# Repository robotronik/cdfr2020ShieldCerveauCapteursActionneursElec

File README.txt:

Ce fichier a pour but d'expliciter les différents composants de la carte électronique afin d'en faciliter la compréhension.

LevelShifter_ToF :

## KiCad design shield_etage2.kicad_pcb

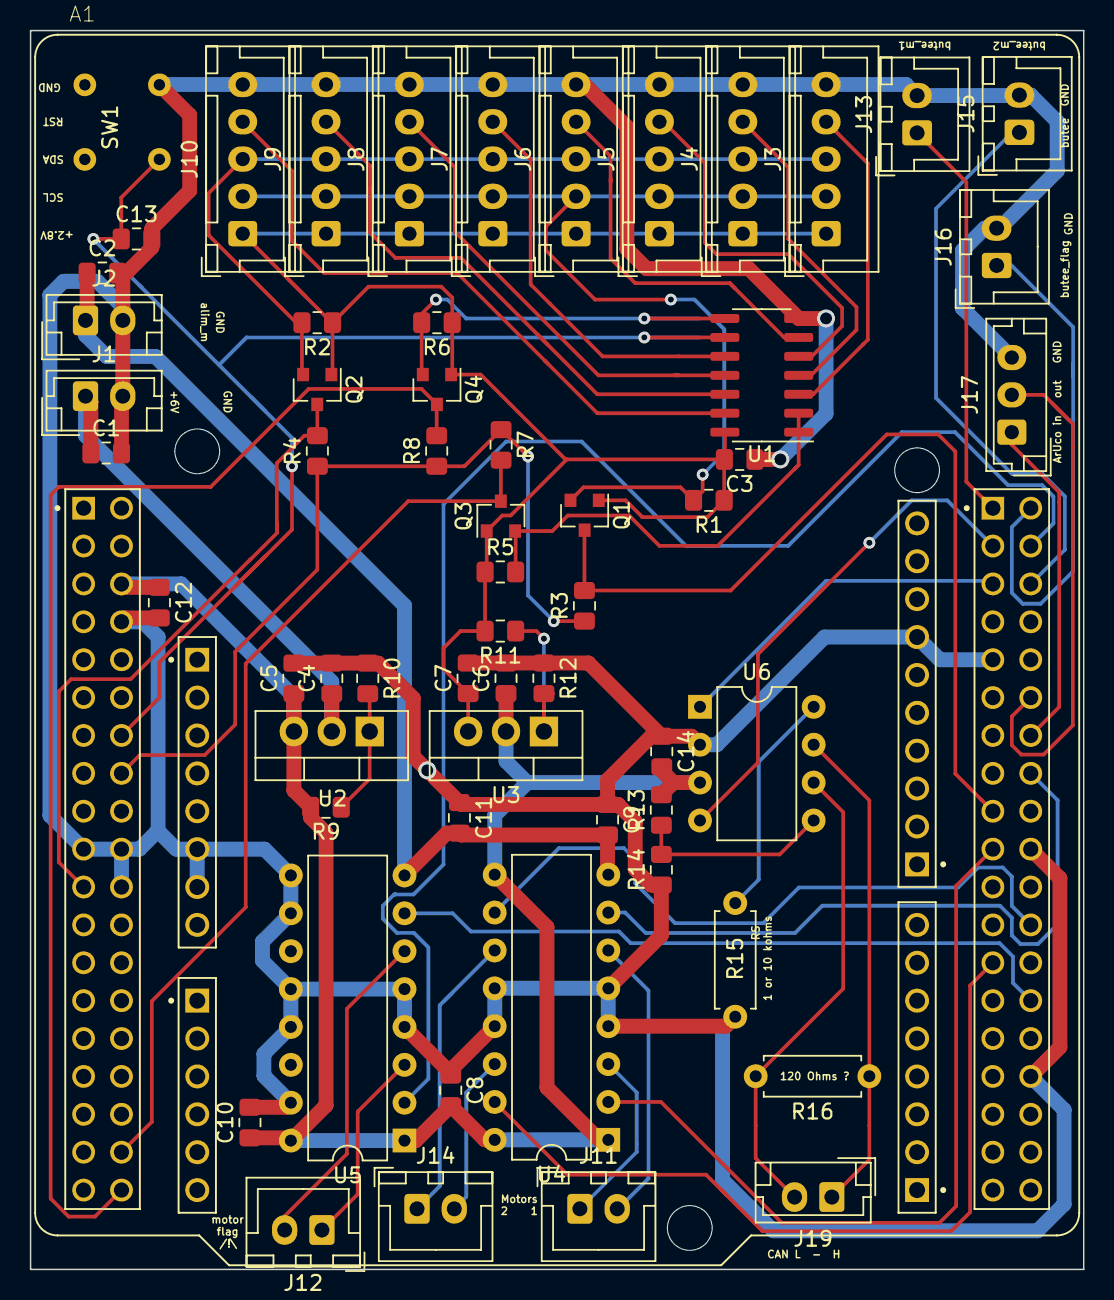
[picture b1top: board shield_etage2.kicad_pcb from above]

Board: 2 copper layers, 70.6 x 83.1 mm, 60 parts (0 on the bottom side), 48 nets.

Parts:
A1: NUCLEO-F401RE; ST_NUCLEO-F401RE
C1, C2, C3, C4, C6, C8, C9, C10, C11, C13, C14: 100n; C_0805_2012Metric_Pad1.15x1.40mm_HandSolder
C5, C7, C12: 1µ; C_0805_2012Metric_Pad1.15x1.40mm_HandSolder
J1, J2: Conn_01x02; JST_EH_B2B-EH-A_1x02_P2.50mm_Vertical
J3, J4, J5, J6, J7, J8, J9, J10: ToF; JST_XH_B5B-XH-A_1x05_P2.50mm_Vertical
J11, J12, J14: Moteur; JST_XH_B2B-XH-A_1x02_P2.50mm_Vertical
J13, J15, J16: butee; JST_XH_B2B-XH-A_1x02_P2.50mm_Vertical
J17: Conn_01x03-Connector_Generic-shield_etage2-rescue; JST_EH_B3B-EH-A_1x03_P2.50mm_Vertical
J19: output_CAN; JST_EH_B2B-EH-A_1x02_P2.50mm_Vertical
Q1, Q2, Q3, Q4: BSS138; SOT-23
R1, R2, R3, R4, R5, R6, R7, R8: Pull; R_0805_2012Metric_Pad1.15x1.40mm_HandSolder
R9: 1k; R_0805_2012Metric_Pad1.15x1.40mm_HandSolder
R10: 3k; R_0805_2012Metric_Pad1.15x1.40mm_HandSolder
R11: 240; R_0805_2012Metric_Pad1.15x1.40mm_HandSolder
R12: 300; R_0805_2012Metric_Pad1.15x1.40mm_HandSolder
R13, R14: 470; R_0805_2012Metric_Pad1.15x1.40mm_HandSolder
R15: 10k; R_Axial_DIN0207_L6.3mm_D2.5mm_P7.62mm_Horizontal
R16: 120; R_Axial_DIN0207_L6.3mm_D2.5mm_P7.62mm_Horizontal
SW1: SW_Push; 5x5
U1: 74HC164; SOIC-14_3.9x8.7mm_P1.27mm
U2, U3: LM317_TO3; TO-220-3_Vertical
U4, U5: L293D; DIP-16_W7.62mm
U6: MCP2551-I-P; DIP-8_W7.62mm

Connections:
+2V8: C3.2, C7.1, J3.1, J4.1, J5.1, J6.1, J7.1, J8.1, J9.1, J10.1, Q1.1, Q2.1, Q3.1, Q4.1, R1.1, R2.1, R5.1, R6.1, R11.2, U1.14, U3.3
+3V3: A1.CN7_16, R3.1, R4.1, R7.1, R8.1
+5V: A1.CN7_6, C5.1, C6.1, C8.2, C10.1, C12.1, C14.2, R9.2, R13.2, U2.3, U3.2, U4.1, U4.9, U4.16, U5.1, U5.16, U6.3
+6V: C1.1, C4.1, J1.1, U2.2
/ArUco.sch/ArUco1: A1.CN10_14, J17.1
/ArUco.sch/ArUco2: A1.CN10_12, J17.2
/Driver_moteurs/moteur1_pin1: J11.1, U4.3
/Driver_moteurs/moteur1_pin2: J11.2, U4.6
/Driver_moteurs/moteur2_pin1: J14.1, U4.11
/Driver_moteurs/moteur2_pin2: J14.2, U4.14
/Driver_moteurs/moteur3_pin1: J12.1, U5.3
/Driver_moteurs/moteur3_pin2: J12.2, U5.6
/Driver_moteurs/pwm_bras1: A1.CN10_19, U4.2
/Driver_moteurs/pwm_bras2: A1.CN10_24, U4.10
/Driver_moteurs/pwm_drapeau: A1.CN10_4, U5.2
/Driver_moteurs/sens_bras1: A1.CN10_16, U4.7
/Driver_moteurs/sens_bras2: A1.CN10_25, U4.15
/Driver_moteurs/sens_drapeau: A1.CN10_28, U5.7
/F4/CAN1_RX: A1.CN10_3, U6.4
/F4/CAN1_TX: A1.CN10_5, U6.1
/F4/NRST: A1.CN7_14, C13.1, SW1.2, U1.9
/FinDeCourse_bras1/STM32_GPIO: A1.CN10_1, J13.1
/FinDeCourse_bras2/STM32_GPIO: A1.CN10_6, J15.1
/FinDeCourse_drapeau/STM32_GPIO: A1.CN10_2, J16.1
/LevelShifter_ShiftRegister/STM32_CP: A1.CN7_38, Q4.3, R8.2
/LevelShifter_ShiftRegister/STM32_DSAB: A1.CN7_36, Q3.3, R7.2
/LevelShifter_ShiftRegister/ShiftRegister_CP: Q4.2, R6.2, U1.8
/LevelShifter_ShiftRegister/ShiftRegister_DSAB: Q3.2, R5.2, U1.1, U1.2
/LevelShifter_ToF_I2C/I2C_SCL_STM32: A1.CN10_17, Q1.3, R3.2
/LevelShifter_ToF_I2C/I2C_SCL_ToF: J3.2, J4.2, J5.2, J6.2, J7.2, J8.2, J9.2, J10.2, Q1.2, R1.2
/LevelShifter_ToF_I2C/I2C_SDA_STM32: A1.CN7_21, Q2.3, R4.2
/LevelShifter_ToF_I2C/I2C_SDA_ToF: J3.3, J4.3, J5.3, J6.3, J7.3, J8.3, J9.3, J10.3, Q2.2, R2.2
/ShiftRegister/Reset_ToF_0: J3.4, U1.3
/ShiftRegister/Reset_ToF_1: J4.4, U1.4
/ShiftRegister/Reset_ToF_2: J5.4, U1.5
/ShiftRegister/Reset_ToF_3: J6.4, U1.6
/ShiftRegister/Reset_ToF_4: J7.4, U1.10
/ShiftRegister/Reset_ToF_5: J8.4, U1.11
/ShiftRegister/Reset_ToF_6: J9.4, U1.12
/ShiftRegister/Reset_ToF_7: J10.4, U1.13
ALIM_MOTEURS: C2.1, C9.2, C11.2, J2.1, U4.8, U5.8
GND: A1.CN5_7, A1.CN6_6, A1.CN6_7, A1.CN7_8, A1.CN7_19, A1.CN7_20, A1.CN7_22, A1.CN10_9, A1.CN10_20, A1.CN10_32, C1.2, C2.2, C3.1, C4.2, C5.2, C6.2, C7.2, C8.1, C9.1, C10.2, C11.1, C12.2, C13.2, C14.1, J1.2, J2.2, J3.5, J4.5, J5.5, J6.5, J7.5, J8.5, J9.5, J10.5, J13.2, J15.2, J16.2, J17.3, R10.1, R12.1, R14.1, R15.2, SW1.1, U1.7, U4.4, U4.5, U4.12, U4.13, U5.4, U5.5, U5.9, U5.10, U5.12, U5.13, U5.15, U6.2
unnamed: J19.1, R16.1, U6.7
unnamed: J19.2, R16.2, U6.6
unnamed: R9.1, R10.2, U2.1
unnamed: R11.1, R12.2, U3.1
unnamed: R13.1, R14.2, U6.5
unnamed: R15.1, U6.8

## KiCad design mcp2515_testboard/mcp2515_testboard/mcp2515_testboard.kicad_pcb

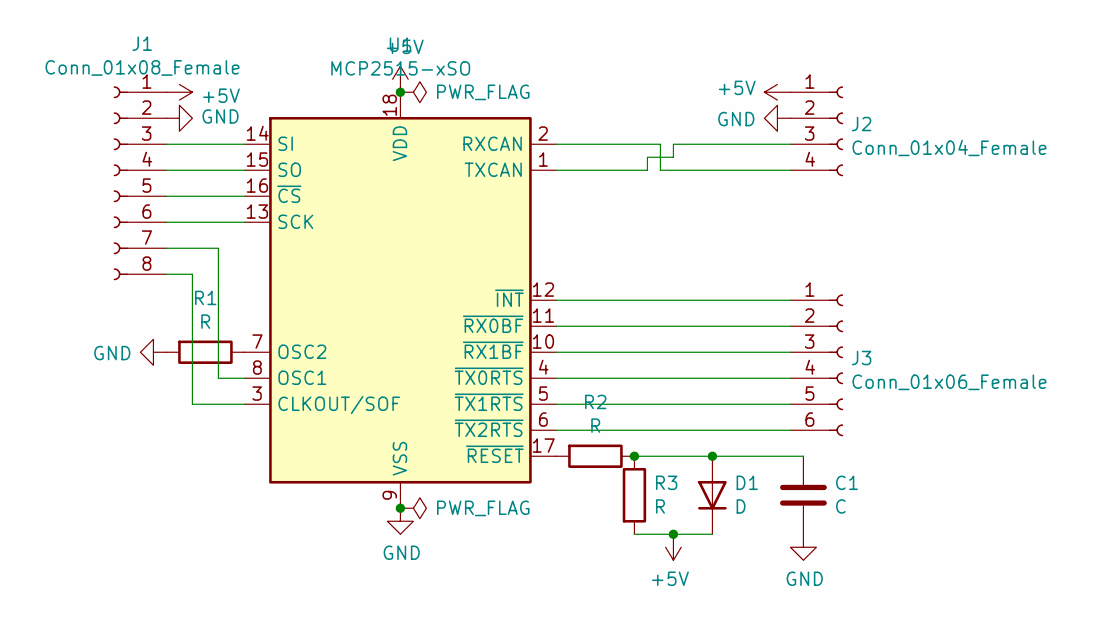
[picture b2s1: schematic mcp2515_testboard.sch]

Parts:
C1: C; C_Rect_L4.0mm_W2.5mm_P2.50mm
D1: D; R_Axial_DIN0207_L6.3mm_D2.5mm_P7.62mm_Horizontal
J1: Conn_01x08_Female; JST_EH_B8B-EH-A_1x08_P2.50mm_Vertical
J2: Conn_01x04_Female; JST_EH_B4B-EH-A_1x04_P2.50mm_Vertical
J3: Conn_01x06_Female; JST_EH_B6B-EH-A_1x06_P2.50mm_Vertical
R1, R2, R3: R; R_Axial_DIN0207_L6.3mm_D2.5mm_P7.62mm_Horizontal
U1: MCP2515-xSO; DIP-18_W7.62mm

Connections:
+5V: D1.1 (K), J1.1, J2.1, R3.2, U1.18 (VDD)
GND: C1.2, J1.2, J2.2, R1.2, U1.9 (VSS)
unnamed: C1.1, D1.2 (A), R2.1, R3.1
unnamed: J1.3, U1.14 (SI)
unnamed: J1.4, U1.15 (SO)
unnamed: J1.5, U1.16 (~CS)
unnamed: J1.6, U1.13 (SCK)
unnamed: J1.7, U1.8 (OSC1)
unnamed: J1.8, U1.3 (CLKOUT/SOF)
unnamed: J2.3, U1.1 (TXCAN)
unnamed: J2.4, U1.2 (RXCAN)
unnamed: J3.1, U1.12 (~INT)
unnamed: J3.2, U1.11 (~RX0BF)
unnamed: J3.3, U1.10 (~RX1BF)
unnamed: J3.4, U1.4 (~TX0RTS)
unnamed: J3.5, U1.5 (~TX1RTS)
unnamed: J3.6, U1.6 (~TX2RTS)
unnamed: R1.1, U1.7 (OSC2)
unnamed: R2.2, U1.17 (~RESET)

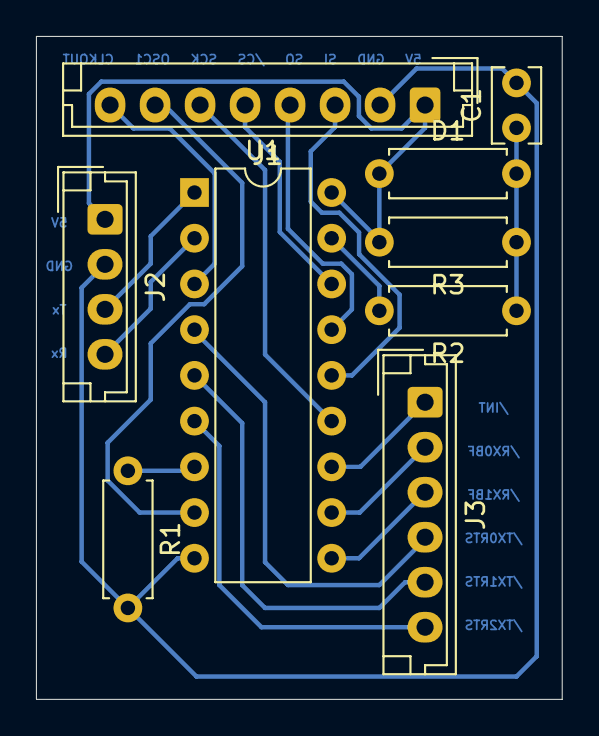
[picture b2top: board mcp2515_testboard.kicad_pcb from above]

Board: 2 copper layers, 29.2 x 36.8 mm, 9 parts (0 on the bottom side), 19 nets.

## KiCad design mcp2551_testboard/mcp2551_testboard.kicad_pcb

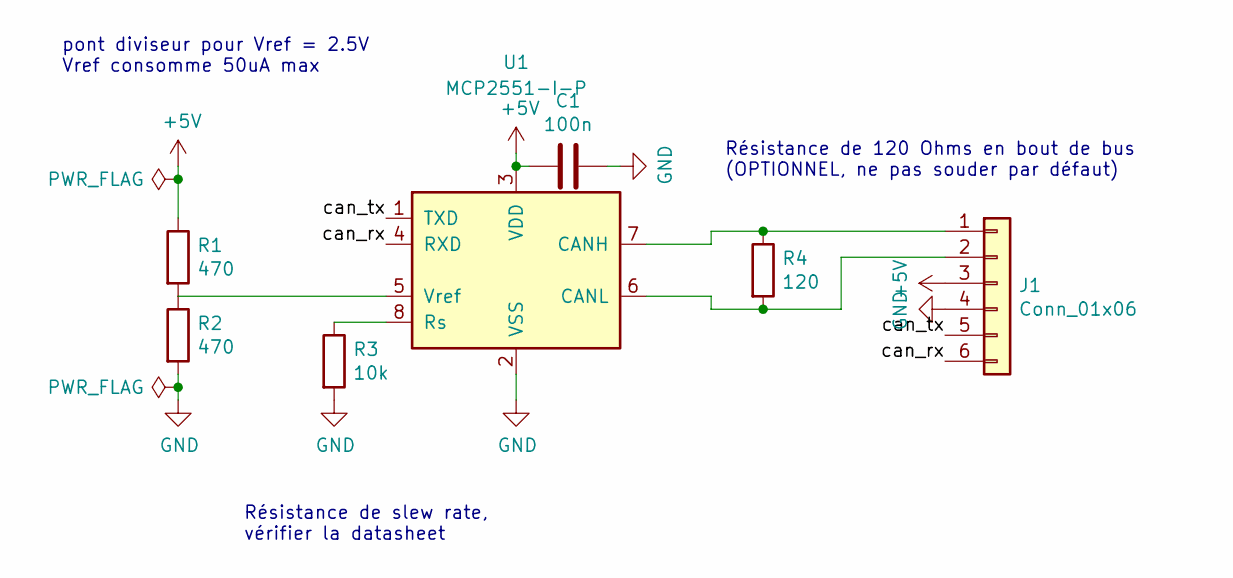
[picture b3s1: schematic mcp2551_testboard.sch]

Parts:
C1: 100n; C_Rect_L4.0mm_W2.5mm_P2.50mm
J1: Conn_01x06; JST_EH_B6B-EH-A_1x06_P2.50mm_Vertical
R1, R2: 470; R_Axial_DIN0207_L6.3mm_D2.5mm_P7.62mm_Horizontal
R3: 10k; R_Axial_DIN0207_L6.3mm_D2.5mm_P7.62mm_Horizontal
R4: 120; R_Axial_DIN0207_L6.3mm_D2.5mm_P7.62mm_Horizontal
U1: MCP2551-I-P; DIP-8_W7.62mm

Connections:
+5V: C1.2, J1.3, R1.1, U1.3 (VDD)
/can_rx: J1.6, U1.4 (RXD)
/can_tx: J1.5, U1.1 (TXD)
GND: C1.1, J1.4, R2.2, R3.2, U1.2 (VSS)
unnamed: J1.1, R4.1, U1.7 (CANH)
unnamed: J1.2, R4.2, U1.6 (CANL)
unnamed: R1.2, R2.1, U1.5 (Vref)
unnamed: R3.1, U1.8 (Rs)

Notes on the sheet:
pont diviseur pour Vref = 2.5V Vref consomme 50uA max
Résistance de 120 Ohms en bout de bus (OPTIONNEL, ne pas souder par défaut)
Résistance de slew rate, vérifier la datasheet

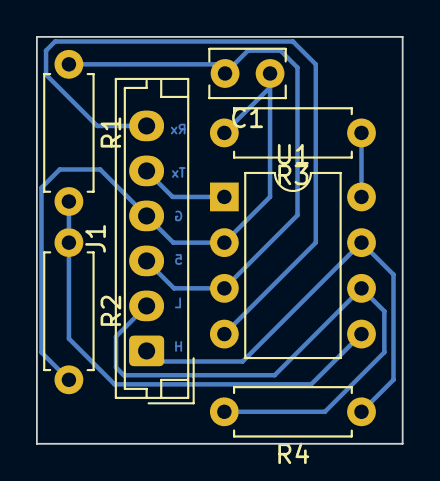
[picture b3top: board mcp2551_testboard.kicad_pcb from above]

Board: 2 copper layers, 20.3 x 22.6 mm, 7 parts (0 on the bottom side), 8 nets.

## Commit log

2020-06-30 avancement général du routage
2020-07-03 première version du routage complète
2020-07-10 Correction de défauts, quelques pistes refaites plus proprement
2020-10-06 Yann Pirot changes in october 2020, added DC motor output for second arm, ArUco 1&1 outputs, rebuilt from scratch, no re-checked
2020-10-08 addition of second motor and ArUco outputs, note the last edition is the one called gange
2020-10-11 removed psi-things pins, added transceiver MCP2551 for CAN, changed motors input protocol, RS must be chosen 1 or 10 kohms, and a foot print for a potentitial 120 ohms resistor is present for CAN bus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
2020-10-11 oops, some component where on the wrong side....
2020-10-15 some tweaks after Xavier's review
2020-10-15 some more changes after Hugo's review, motors connectors not updated
2020-10-15 added ganged testboard for mcp2551
2021-01-28 ajout de la pcb de test pour mcp2515, pas de doc
2021-03-18 ajout du petit calcul pour la valeur des compos
2021-04-10 correction mm -> inch, empreinte du bouton
